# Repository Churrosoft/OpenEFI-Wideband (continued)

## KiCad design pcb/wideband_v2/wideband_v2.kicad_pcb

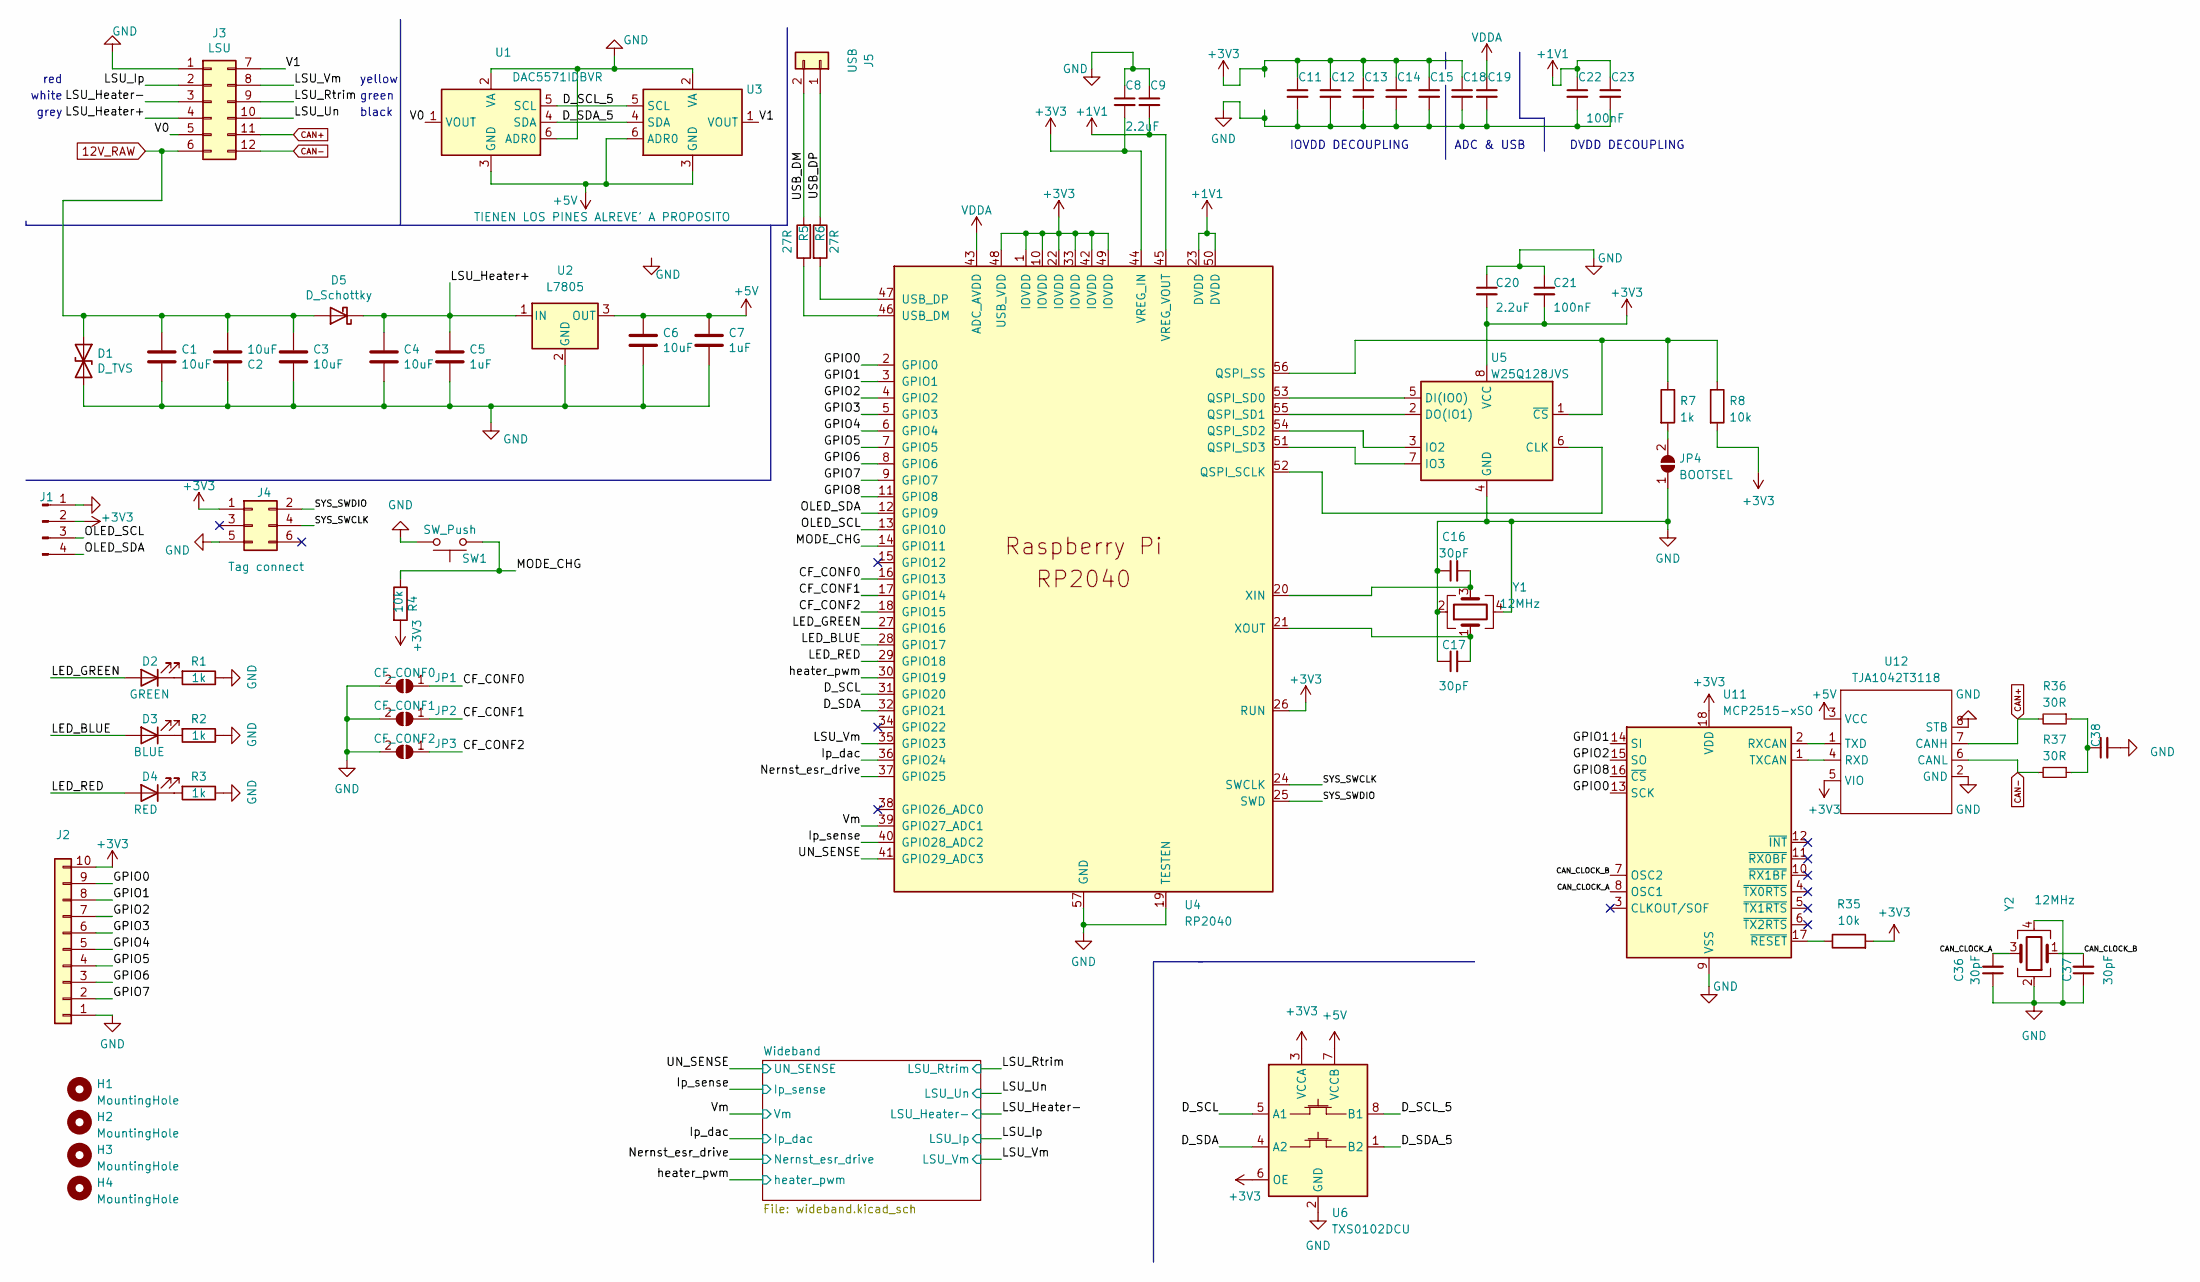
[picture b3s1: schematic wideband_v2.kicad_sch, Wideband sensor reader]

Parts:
C1, C2, C3, C4, C6: 10uF; C_1206_3216Metric; LCSC C13585
C5, C7: 1uF; C_0603_1608Metric; LCSC C15849
C8, C9, C20: 2.2uF; C_0603_1608Metric
C11, C12, C13, C14, C15, C18, C19, C21, C22, C23: 100nF; C_0603_1608Metric
C16, C17, C36, C37: 30pF; C_0603_1608Metric
C38: 4.7nF; C_0805_2012Metric; LCSC C77475
D1: D_TVS; D_SMC; LCSC C151279
D2: GREEN; LED_0603_1608Metric; LCSC C72043
D3: BLUE; LED_0603_1608Metric; LCSC C72041
D4: RED; LED_0603_1608Metric; LCSC C72041
D5: D_Schottky; D_SMA; LCSC C22452
H1, H2, H3, H4: MountingHole; MountingHole_2.2mm_M2
J1: DISPLAY; PinHeader_1x04_P2.54mm_Vertical
J2: GPIO; PinHeader_1x10_P2.00mm_Vertical
J3: LSU; Molex_Mini-Fit_Jr_5566-12A2_2x06_P4.20mm_Vertical
J4: Tag connect; Tag-Connect_TC2030-IDC-NL_2x03_P1.27mm_Vertical
J5: USB; PinHeader_1x02_P2.00mm_Vertical
JP1: CF_CONF0; SolderJumper-2_P1.3mm_Open_TrianglePad1.0x1.5mm
JP2: CF_CONF1; SolderJumper-2_P1.3mm_Open_TrianglePad1.0x1.5mm
JP3: CF_CONF2; SolderJumper-2_P1.3mm_Open_TrianglePad1.0x1.5mm
JP4: BOOTSEL; SolderJumper-2_P1.3mm_Open_TrianglePad1.0x1.5mm
R1, R2, R3, R7: 1k; R_0603_1608Metric
R4: 10k; R_0603_1608Metric; LCSC C25744
R5, R6: 27R; R_0603_1608Metric
R8, R35: 10k; R_0603_1608Metric
R36, R37: 30R; R_1206_3216Metric; LCSC C205298
SW1: SW_Push; SW_Tactile_SPST_Angled_PTS645Vx83-2LFS
U1: DAC5571IDBVR; SOT-23-6
U2: L7805; TO-220-3_Vertical
U3: DAC5571IDBVR; SOT-23-6; LCSC C24061
U4: RP2040; RP2040-QFN-56
U5: W25Q128JVS; SOIC-8_5.23x5.23mm_P1.27mm
U6: TXS0102DCU; VSSOP-8_2.3x2mm_P0.5mm
U11: MCP2515-xSO; SOIC-18W_7.5x11.6mm_P1.27mm
U12: TJA1042T3118; HTSOP-8-1EP_3.9x4.9mm_P1.27mm_EP2.4x3.2mm
Y1, Y2: 12MHz; Crystal_SMD_3225-4Pin_3.2x2.5mm; LCSC C9002

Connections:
12V_RAW: C1.1, C2.2, C3.1, D1.1 (A1), D5.2 (A), J3.6
+1V1: C9.2, C22.1, C23.1, U4.23 (DVDD), U4.45 (VREG_VOUT), U4.50 (DVDD)
+3V3: C8.2, C11.1, C12.1, C13.1, C14.1, C15.1, C18.1, C20.2, C21.2, J1.2, J2.10, J4.1, R4.2, R8.2, R35.2, U4.1 (IOVDD), U4.10 (IOVDD), U4.22 (IOVDD), U4.26 (RUN), U4.33 (IOVDD), U4.42 (IOVDD), U4.44 (VREG_IN), U4.48 (USB_VDD), U4.49 (IOVDD), U5.8 (VCC), U6.3 (VCCA), U6.6 (OE), U11.18 (VDD), U12.5 (VIO); also elsewhere on the board
+5V: C6.1, C7.1, U1.3 (GND), U2.3 (OUT), U3.3 (GND), U3.6 (ADR0), U6.7 (VCCB), U12.3 (VCC); also elsewhere on the board
/CAN_CLOCK_A: C36.2, U11.8 (OSC1), Y2.3
/CAN_CLOCK_B: C37.2, U11.7 (OSC2), Y2.1
/CF_CONF0: JP1.1 (A), U4.16 (GPIO13)
/CF_CONF1: JP2.1 (A), U4.17 (GPIO14)
/CF_CONF2: JP3.1 (A), U4.18 (GPIO15)
/D_SCL: U4.31 (GPIO20), U6.5 (A1)
/D_SCL_5: U1.5 (SCL), U3.5 (SCL), U6.8 (B1)
/D_SDA: U4.32 (GPIO21), U6.4 (A2)
/D_SDA_5: U1.4 (SDA), U3.4 (SDA), U6.1 (B2)
/GPIO0: J2.9, U4.2 (GPIO0), U11.13 (SCK)
/GPIO1: J2.8, U4.3 (GPIO1), U11.14 (SI)
/GPIO2: J2.7, U4.4 (GPIO2), U11.15 (SO)
/GPIO3: J2.6, U4.5 (GPIO3)
/GPIO4: J2.5, U4.6 (GPIO4)
/GPIO5: J2.4, U4.7 (GPIO5)
/GPIO6: J2.3, U4.8 (GPIO6)
/GPIO7: J2.2, U4.9 (GPIO7)
/GPIO8: U4.11 (GPIO8), U11.16 (~CS)
/Ip_dac: U4.36 (GPIO24); also elsewhere on the board
/Ip_sense: U4.40 (GPIO28_ADC2); also elsewhere on the board
/LED_BLUE: D3.2 (A), U4.28 (GPIO17)
/LED_GREEN: D2.2 (A), U4.27 (GPIO16)
/LED_RED: D4.2 (A), U4.29 (GPIO18)
/LSU_Heater+: C4.1, C5.1, D5.1 (K), J3.4, U2.1 (IN)
/LSU_Heater-: J3.3; also elsewhere on the board
/LSU_Ip: J3.2; also elsewhere on the board
/LSU_Rtrim: J3.9; also elsewhere on the board
/LSU_Un: J3.10; also elsewhere on the board
/LSU_Vm: J3.8, U4.35 (GPIO23); also elsewhere on the board
/MODE_CHG: R4.1, SW1.1, U4.14 (GPIO11)
/Nernst_esr_drive: U4.37 (GPIO25); also elsewhere on the board
/OLED_SCL: J1.3, U4.13 (GPIO10)
/OLED_SDA: J1.4, U4.12 (GPIO9)
/SYS_SWCLK: J4.4, U4.24 (SWCLK)
/SYS_SWDIO: J4.2, U4.25 (SWD)
/UN_SENSE: U4.41 (GPIO29_ADC3); also elsewhere on the board
/USB_DM: J5.2, R5.2
/USB_DP: J5.1, R6.1
/V0: J3.5, U1.1 (VOUT)
/V1: J3.7, U3.1 (VOUT)
/Vm: U4.39 (GPIO27_ADC1); also elsewhere on the board
/heater_pwm: U4.30 (GPIO19); also elsewhere on the board
CAN+: J3.11, R36.2, U12.7 (CANH)
CAN-: J3.12, R37.2, U12.6 (CANL)
GND: C1.2, C2.1, C3.2, C4.2, C5.2, C6.2, C7.2, C8.1, C9.1, C11.2, C12.2, C13.2, C14.2, C15.2, C16.1, C17.1, C18.2, C19.2, C20.1, C21.1, C22.2, C23.2, C36.1, C37.1, C38.2, D1.2 (A2), J1.1, J2.1, J3.1, J4.5, JP1.2 (B), JP2.2 (B), JP3.2 (B), JP4.1 (A), R1.1, R2.1, R3.1, SW1.2, U1.2 (VA), U1.6 (ADR0), U2.2 (GND), U3.2 (VA), U4.19 (TESTEN), U4.57 (GND), U5.4 (GND), U6.2 (GND), U11.9 (VSS), U12.2 (GND), U12.8 (STB), Y1.2, Y1.4, Y2.2, Y2.4; also elsewhere on the board
unnamed: C16.2, U4.20 (XIN), Y1.3
unnamed: C17.2, U4.21 (XOUT), Y1.1
unnamed: C38.1, R36.1, R37.1
unnamed: D2.1 (K), R1.2
unnamed: D3.1 (K), R2.2
unnamed: D4.1 (K), R3.2
unnamed: JP4.2 (B), R7.2
unnamed: R5.1, U4.46 (USB_DM)
unnamed: R6.2, U4.47 (USB_DP)
unnamed: R7.1, R8.1, U4.56 (QSPI_SS), U5.1 (~CS)
unnamed: R35.1, U11.17 (~RESET)
unnamed: U4.51 (QSPI_SD3), U5.7 (IO3)
unnamed: U4.52 (QSPI_SCLK), U5.6 (CLK)
unnamed: U4.53 (QSPI_SD0), U5.5 (DI(IO0))
unnamed: U4.54 (QSPI_SD2), U5.3 (IO2)
unnamed: U4.55 (QSPI_SD1), U5.2 (DO(IO1))
unnamed: U11.1 (TXCAN), U12.4 (RXD)
unnamed: U11.2 (RXCAN), U12.1 (TXD)
VDDA: C19.1, U4.43 (ADC_AVDD); also elsewhere on the board

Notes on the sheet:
grey
ADC & USB
black
white
red
IOVDD DECOUPLING
yellow
DVDD DECOUPLING
green

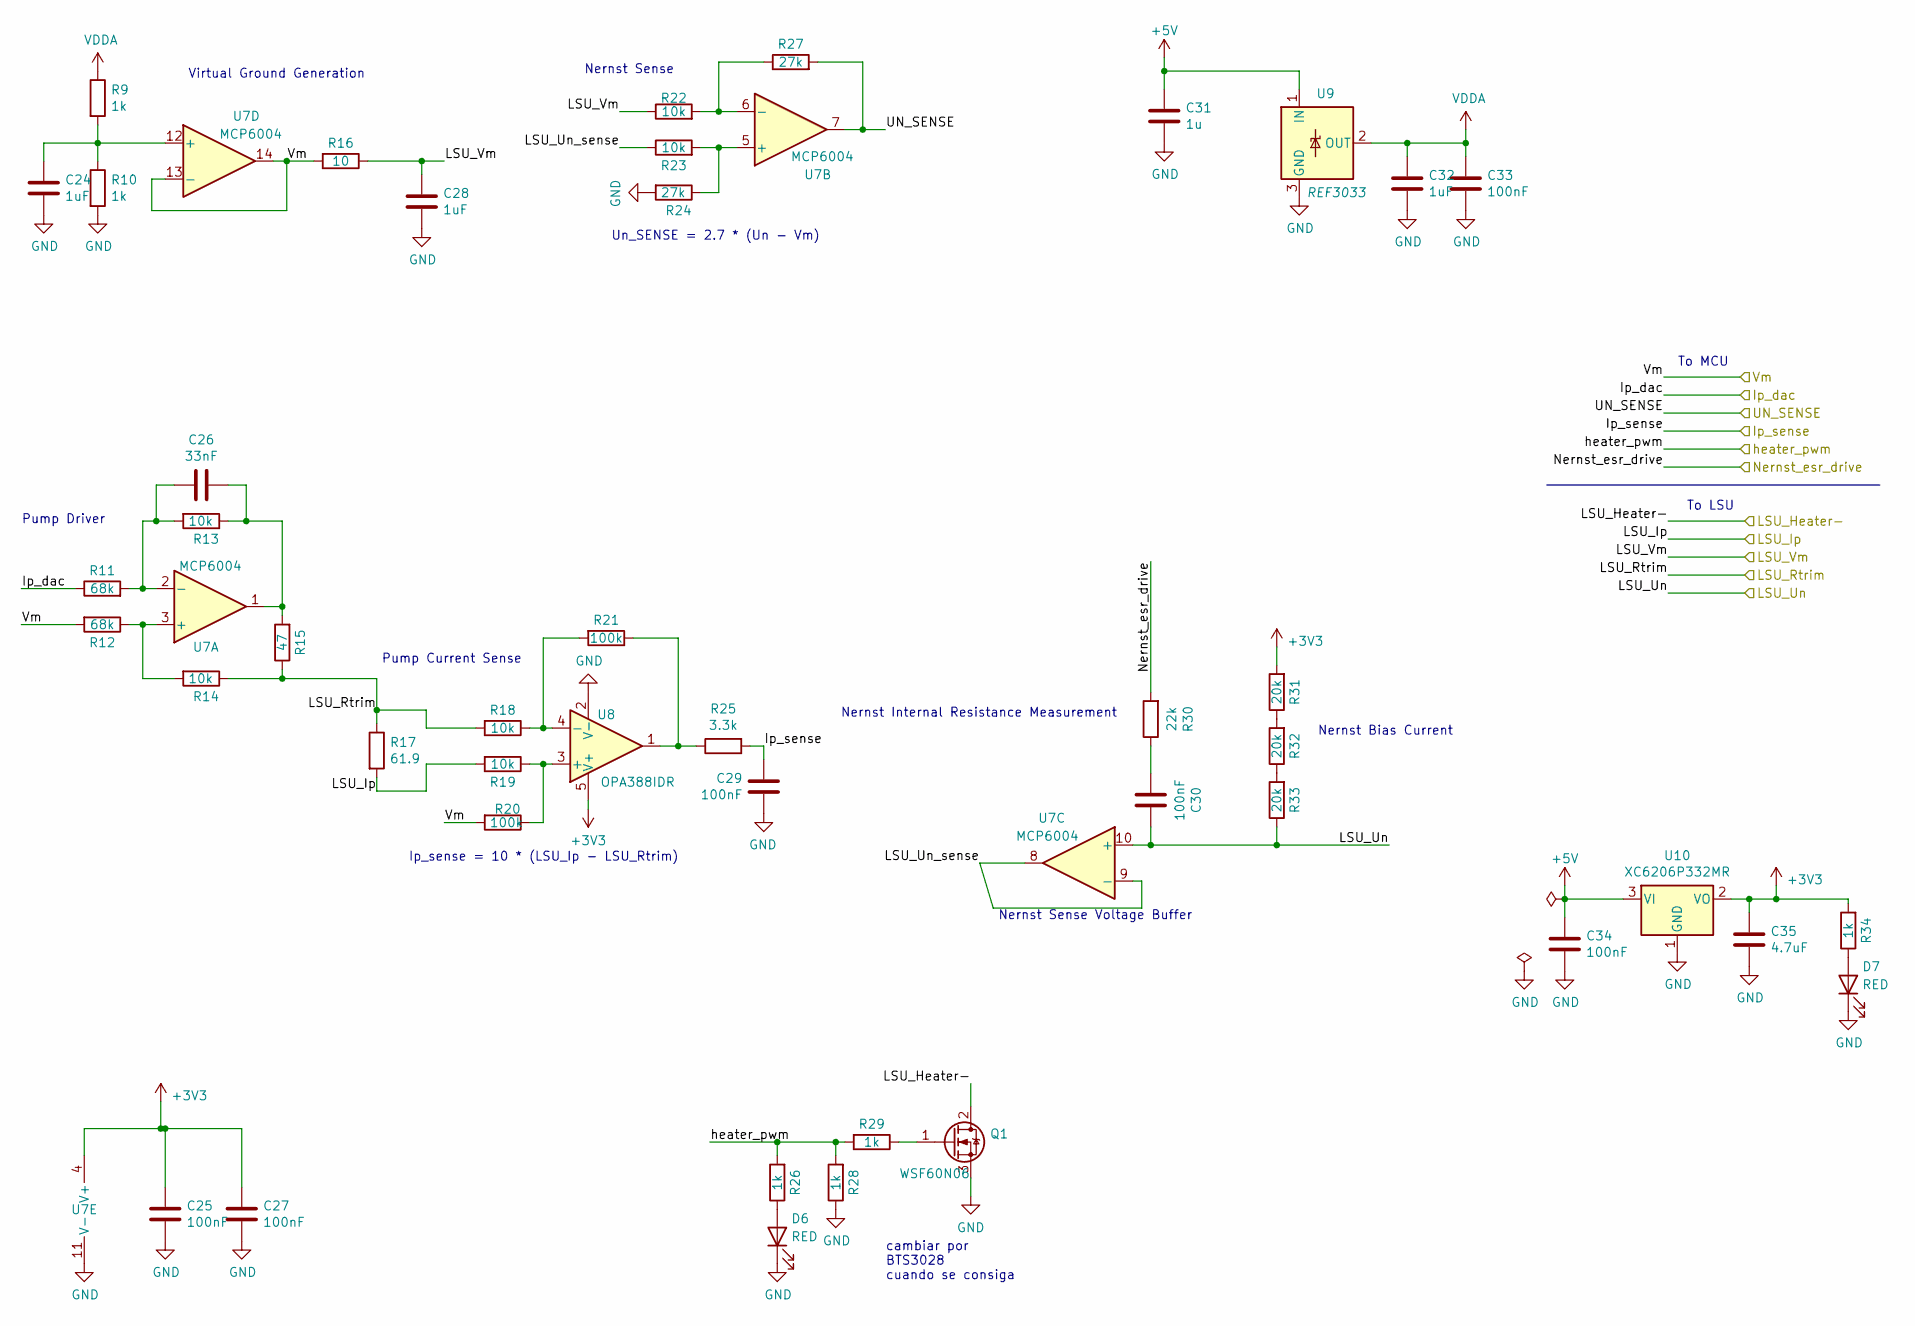
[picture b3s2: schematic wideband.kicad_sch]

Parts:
C24, C28, C32: 1uF; R_0603_1608Metric; LCSC C52923
C25, C27, C29, C30, C33, C34: 100nF; R_0603_1608Metric; LCSC C1525
C26: 33nF; R_0603_1608Metric; LCSC C1585
C31: 1u; R_0603_1608Metric; LCSC C52923
C35: 4.7uF; C_0603_1608Metric; LCSC C19666
D6, D7: RED; LED_0603_1608Metric; LCSC C2286
Q1: WSF60N06; TO-252-2; LCSC C148432
R9, R10, R26, R28, R29, R34: 1k; R_0603_1608Metric; LCSC C11702
R11, R12: 68k; R_0603_1608Metric; LCSC C36871
R13, R14, R18, R19, R22, R23: 10k; R_0603_1608Metric; LCSC C25744
R15: 47; R_0603_1608Metric; LCSC C25118
R16: 10; R_0603_1608Metric; LCSC C25077
R17: 61.9; R_0603_1608Metric; LCSC C23092
R20, R21: 100k; R_0603_1608Metric; LCSC C25741
R24, R27: 27k; R_0603_1608Metric; LCSC C25771
R25: 3.3k; R_0603_1608Metric; LCSC C25890
R30: 22k; R_0603_1608Metric; LCSC C25768
R31, R32, R33: 20k; R_0603_1608Metric; LCSC C25765
U7: MCP6004; TSSOP-14_4.4x5mm_P0.65mm; LCSC C50282
U8: OPA388IDR; TSOT-23-5; LCSC C154118
U9: REF3033; SOT-23; LCSC C36658
U10: XC6206P332MR; SOT-23; LCSC C5446

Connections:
+3V3: C25.1, C27.1, C35.1, R31.2, R34.2, U7.4 (V+), U8.5 (V+), U10.2 (VO); also elsewhere on the board
+5V: C31.1, C34.1, U9.1 (IN), U10.3 (VI); also elsewhere on the board
/Ip_dac: R11.1; also elsewhere on the board
/Ip_sense: C29.1, R25.2; also elsewhere on the board
/LSU_Heater-: Q1.2 (D); also elsewhere on the board
/LSU_Ip: R17.2, R19.2; also elsewhere on the board
/LSU_Rtrim: R14.1, R15.1, R17.1, R18.2; also elsewhere on the board
/LSU_Un: C30.1, R33.1, U7.10 (+); also elsewhere on the board
/LSU_Vm: C28.1, R16.1, R22.1; also elsewhere on the board
/Nernst_esr_drive: R30.2; also elsewhere on the board
/UN_SENSE: R27.2, U7.7; also elsewhere on the board
/Vm: R12.2, R16.2, R20.2, U7.13 (-), U7.14; also elsewhere on the board
/Wideband/LSU_Un_sense: R23.1, U7.8, U7.9 (-)
/heater_pwm: R26.2, R28.2, R29.2; also elsewhere on the board
GND: C24.2, C25.2, C27.2, C28.2, C29.2, C31.2, C32.2, C33.2, C34.2, C35.2, D6.1 (K), D7.1 (K), Q1.3 (S), R10.2, R24.2, R28.1, U7.11 (V-), U8.2 (V-), U9.3 (GND), U10.1 (GND); also elsewhere on the board
unnamed: C24.1, R9.2, R10.1, U7.12 (+)
unnamed: C26.1, R13.1, R15.2, U7.1
unnamed: C26.2, R11.2, R13.2, U7.2 (-)
unnamed: C30.2, R30.1
unnamed: D6.2 (A), R26.1
unnamed: D7.2 (A), R34.1
unnamed: Q1.1 (G), R29.1
unnamed: R12.1, R14.2, U7.3 (+)
unnamed: R18.1, R21.2, U8.4 (-)
unnamed: R19.1, R20.1, U8.3 (+)
unnamed: R21.1, R25.1, U8.1
unnamed: R22.2, R27.1, U7.6 (-)
unnamed: R23.2, R24.1, U7.5 (+)
unnamed: R31.1, R32.2
unnamed: R32.1, R33.2
VDDA: C32.1, C33.1, R9.1, U9.2 (OUT); also elsewhere on the board

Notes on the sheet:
Nernst Sense
Nernst Internal Resistance Measurement
Virtual Ground Generation
To LSU
Nernst Sense Voltage Buffer
Nernst Bias Current
Pump Driver
cambiar por BTS3028 cuando se consiga
Ip_sense = 10 * (LSU_Ip - LSU_Rtrim)
To MCU
Un_SENSE = 2.7 * (Un - Vm)
Pump Current Sense

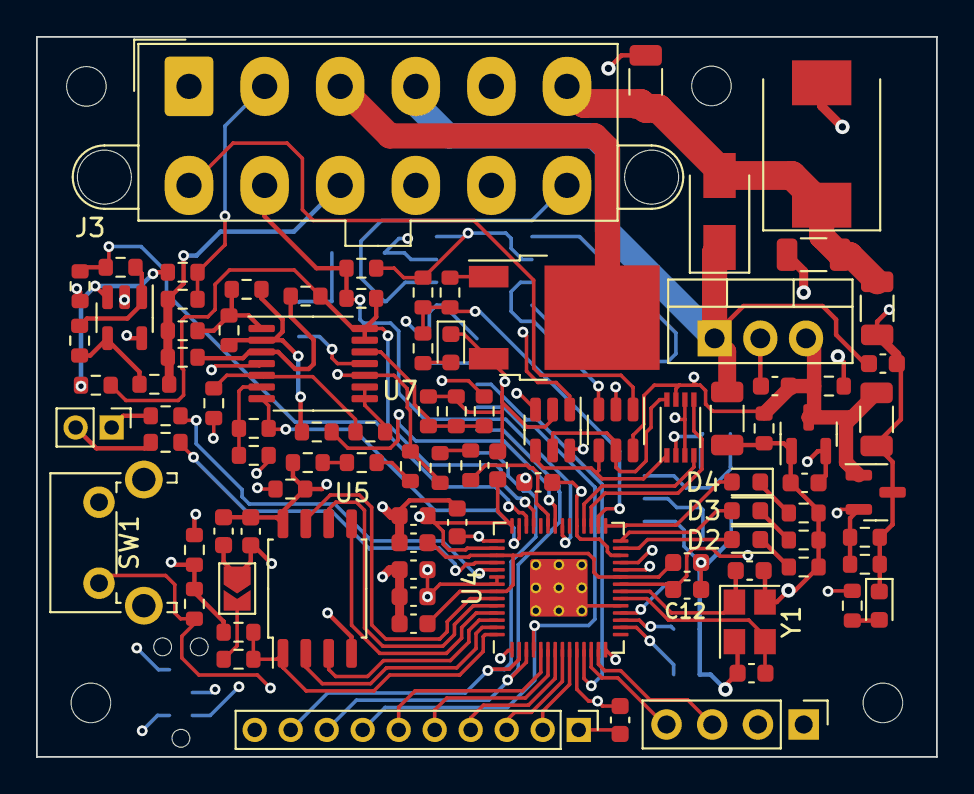
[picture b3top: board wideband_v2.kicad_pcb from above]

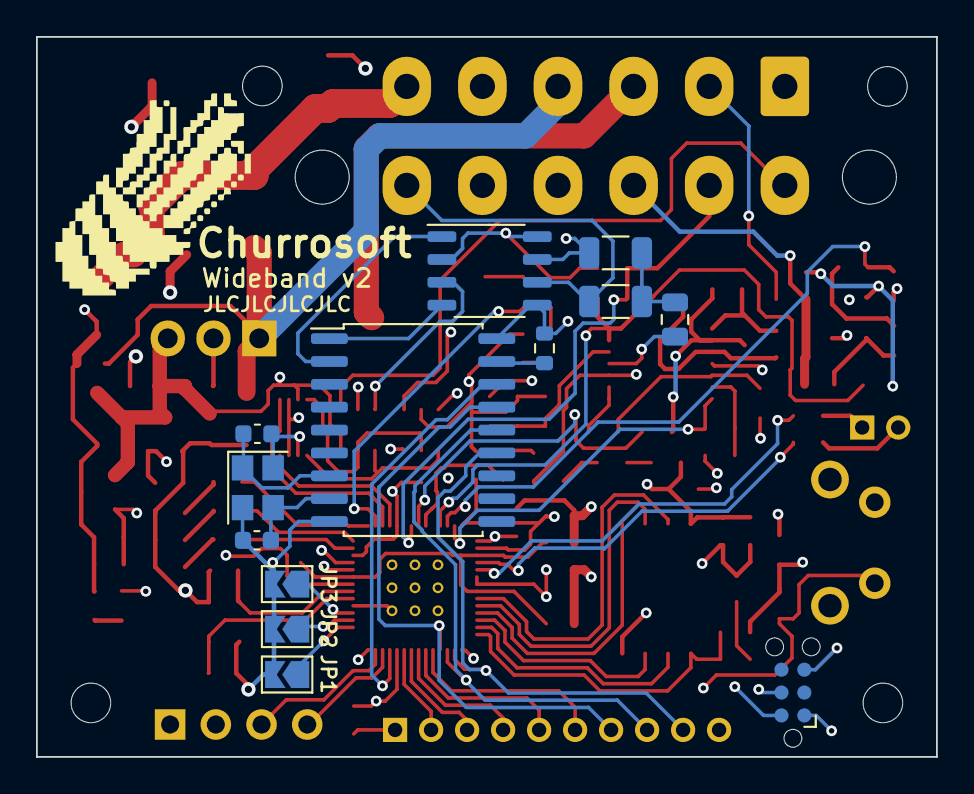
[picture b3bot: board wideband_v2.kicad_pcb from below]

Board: 4 copper layers, 50.0 x 40.0 mm, 111 parts (14 on the bottom side), 84 nets.

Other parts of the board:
Churrosoft: SYM_Hot_Large; churro_new_v4

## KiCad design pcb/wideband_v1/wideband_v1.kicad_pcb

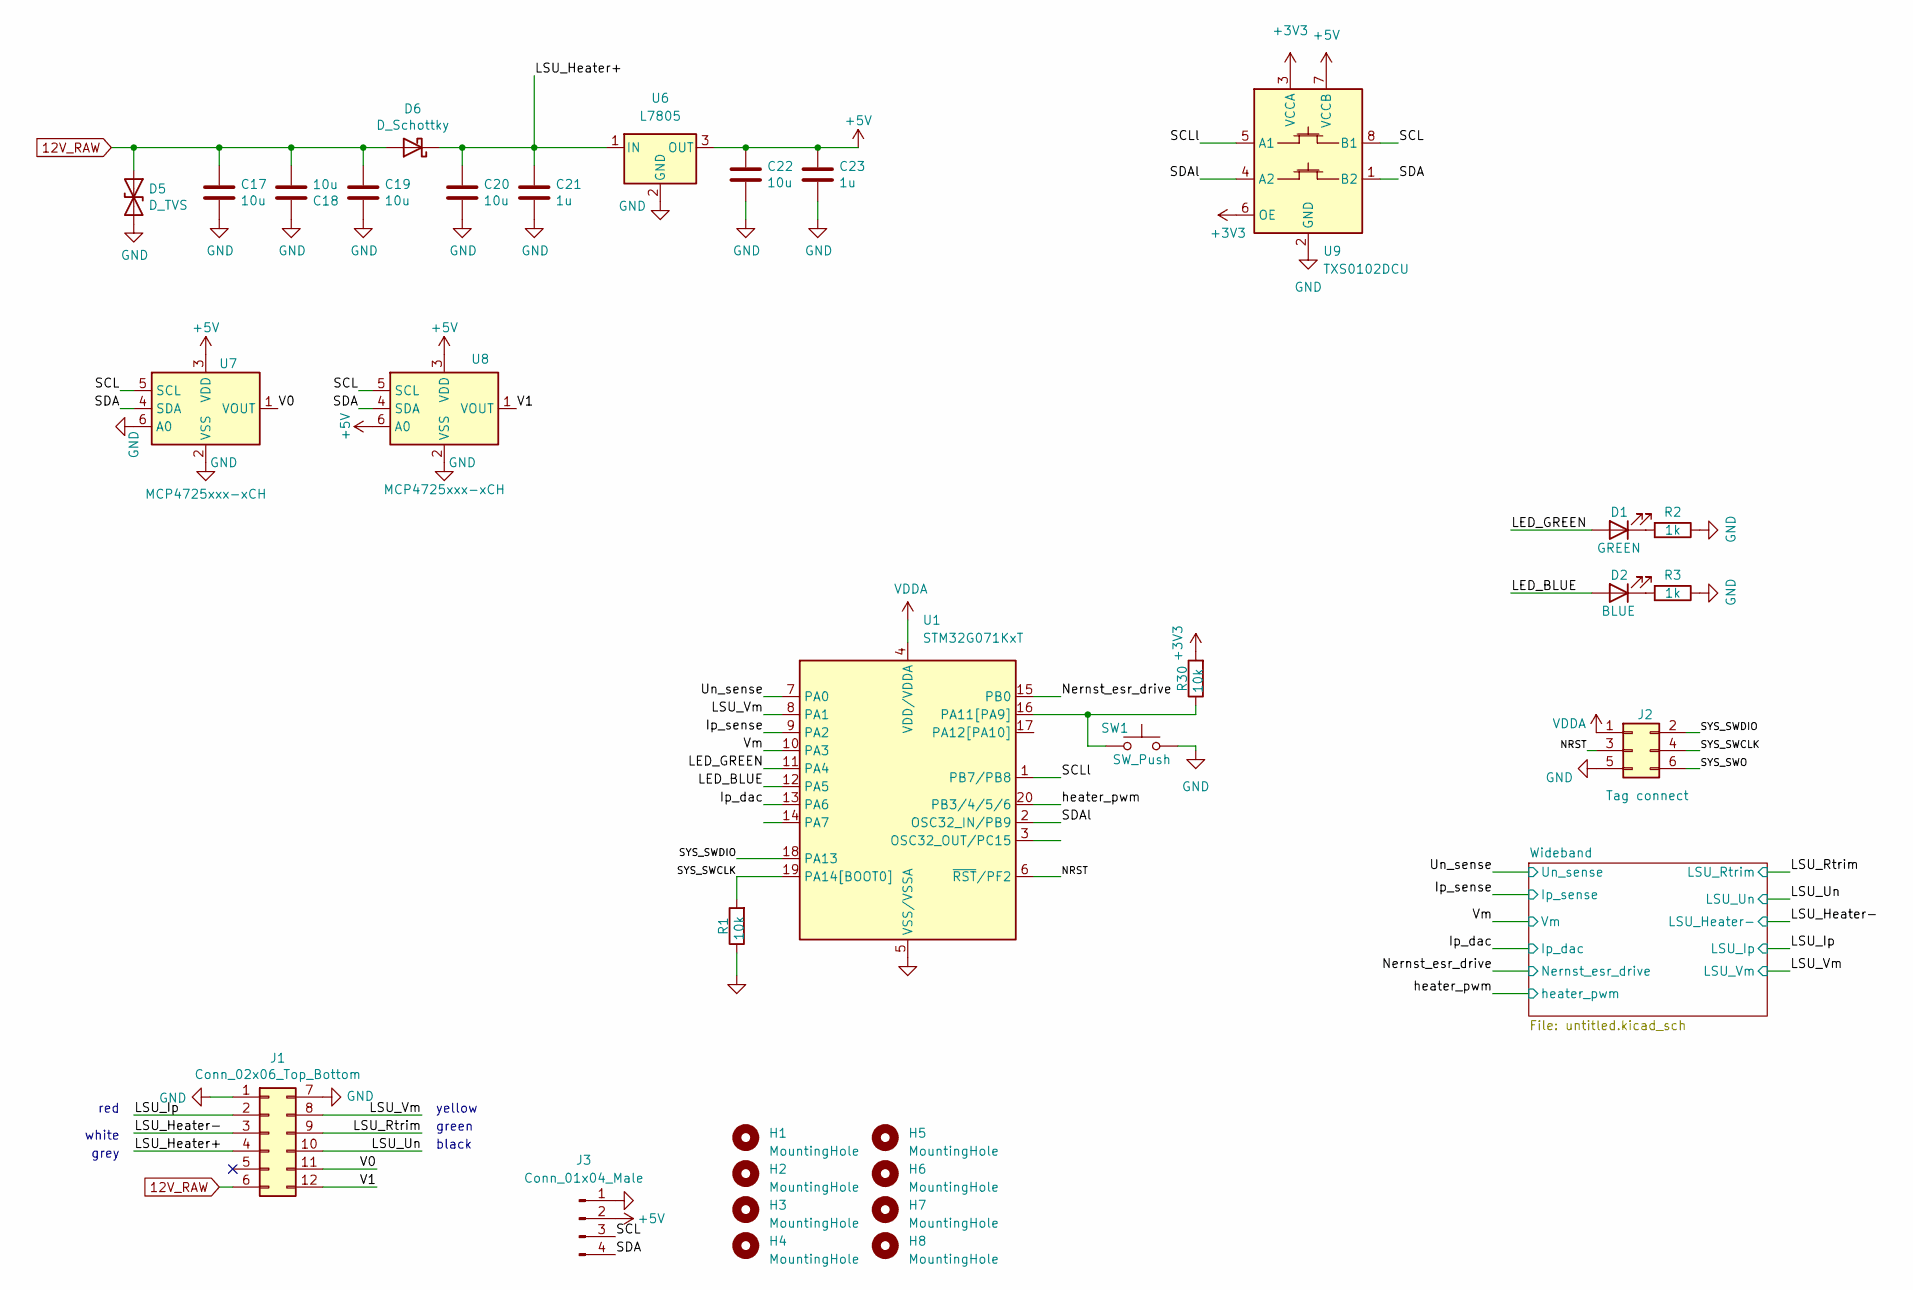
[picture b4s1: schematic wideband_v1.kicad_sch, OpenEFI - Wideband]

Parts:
C17, C18, C19, C20, C22: 10u; C_1206_3216Metric; LCSC C13585
C21, C23: 1u; C_0603_1608Metric; LCSC C15849
D1: GREEN; LED_0603_1608Metric; LCSC C72043
D2: BLUE; LED_0603_1608Metric; LCSC C72041
D5: D_TVS; D_SMC; LCSC C151279
D6: D_Schottky; D_SMA; LCSC C22452
H1, H2, H3, H4: MountingHole; MountingHole_2.2mm_M2
H5, H6, H7, H8: MountingHole; Fiducial_1mm_Mask2mm
J1: Conn_02x06_Top_Bottom; Molex_Mini-Fit_Jr_5566-12A2_2x06_P4.20mm_Vertical
J2: Tag connect; Tag-Connect_TC2030-IDC-NL_2x03_P1.27mm_Vertical
J3: Conn_01x04_Male; PinHeader_1x04_P2.54mm_Vertical
R1, R30: 10k; R_0603_1608Metric; LCSC C25744
R2, R3: 1k; R_0603_1608Metric; LCSC C11702
SW1: SW_Push; SW_Tactile_SPST_Angled_PTS645Vx83-2LFS
U1: STM32G071KxT; TSSOP-20_4.4x6.5mm_P0.65mm
U6: L7805; TO-220-3_Vertical
U7, U8: MCP4725xxx-xCH; SOT-23-6
U9: TXS0102DCU; VSSOP-8_2.3x2mm_P0.5mm

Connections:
12V_RAW: C17.1, C18.2, C19.1, D5.1 (A1), D6.2 (A), J1.6
+5V: C22.1, C23.1, J3.2, U6.3 (OUT), U7.3 (VDD), U8.3 (VDD), U8.6 (A0), U9.7 (VCCB); also elsewhere on the board
/Ip_dac: U1.13 (PA6); also elsewhere on the board
/Ip_sense: U1.9 (PA2); also elsewhere on the board
/LED_BLUE: D2.2 (A), U1.12 (PA5)
/LED_GREEN: D1.2 (A), U1.11 (PA4)
/LSU_Heater+: C20.1, C21.1, D6.1 (K), J1.4, U6.1 (IN)
/LSU_Heater-: J1.3; also elsewhere on the board
/LSU_Ip: J1.2; also elsewhere on the board
/LSU_Rtrim: J1.9; also elsewhere on the board
/LSU_Un: J1.10; also elsewhere on the board
/LSU_Vm: J1.8, U1.8 (PA1); also elsewhere on the board
/NRST: J2.3, U1.6 (~RST/PF2)
/Nernst_esr_drive: U1.15 (PB0); also elsewhere on the board
/SCL: J3.3, U7.5 (SCL), U8.5 (SCL), U9.8 (B1)
/SCLl: U1.1 (PB7/PB8), U9.5 (A1)
/SDA: J3.4, U7.4 (SDA), U8.4 (SDA), U9.1 (B2)
/SDAl: U1.2 (OSC32_IN/PB9), U9.4 (A2)
/SYS_SWCLK: J2.4, R1.2, U1.19 (PA14[BOOT0])
/SYS_SWDIO: J2.2, U1.18 (PA13)
/SYS_SWO: J2.6
/Un_sense: U1.7 (PA0); also elsewhere on the board
/V0: J1.11, U7.1 (VOUT)
/V1: J1.12, U8.1 (VOUT)
/Vm: U1.10 (PA3); also elsewhere on the board
/heater_pwm: U1.20 (PB3/4/5/6); also elsewhere on the board
GND: C17.2, C18.1, C19.2, C20.2, C21.2, C22.2, C23.2, D5.2 (A2), J1.1, J1.7, J2.5, J3.1, R1.1, R2.1, R3.1, SW1.2, U1.5 (VSS/VSSA), U6.2 (GND), U7.2 (VSS), U7.6 (A0), U8.2 (VSS), U9.2 (GND); also elsewhere on the board
unnamed: D1.1 (K), R2.2
unnamed: D2.1 (K), R3.2
unnamed: R30.1, SW1.1, U1.16 (PA11[PA9])
VDDA: J2.1, U1.4 (VDD/VDDA); also elsewhere on the board

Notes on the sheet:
white
yellow
black
green
red
grey

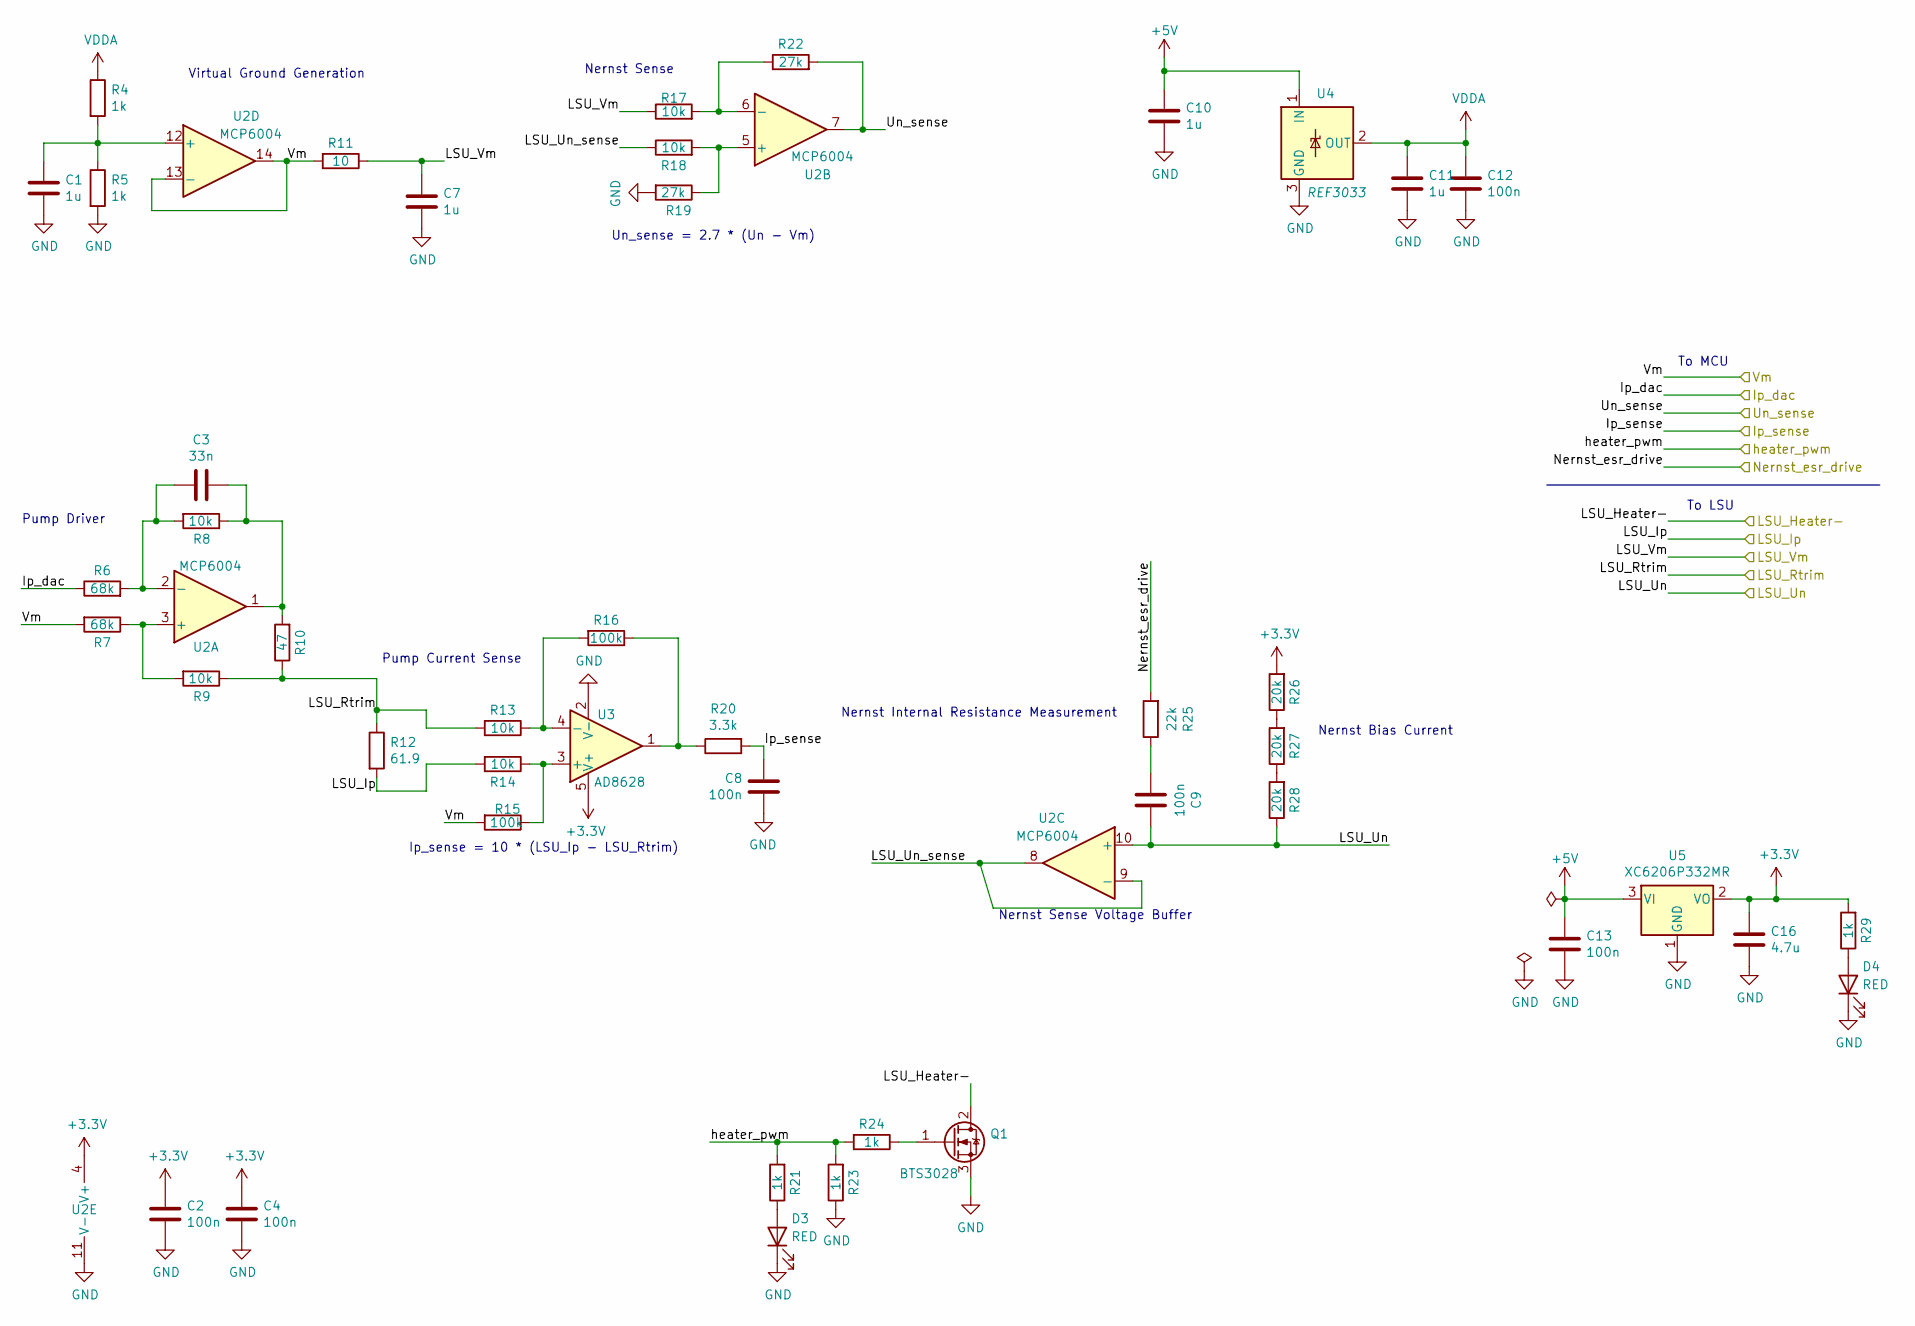
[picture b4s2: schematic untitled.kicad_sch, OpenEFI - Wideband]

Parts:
C1, C7, C10, C11: 1u; R_0603_1608Metric; LCSC C52923
C2, C4, C8, C9, C12, C13: 100n; R_0603_1608Metric; LCSC C1525
C3: 33n; R_0603_1608Metric; LCSC C1585
C16: 4.7u; C_0603_1608Metric; LCSC C19666
D3, D4: RED; LED_0603_1608Metric; LCSC C2286
Q1: BTS3028; TO-252-2; LCSC C112639
R4, R5, R21, R23, R24, R29: 1k; R_0603_1608Metric; LCSC C11702
R6, R7: 68k; R_0603_1608Metric; LCSC C36871
R8, R9, R13, R14, R17, R18: 10k; R_0603_1608Metric; LCSC C25744
R10: 47; R_0603_1608Metric; LCSC C25118
R11: 10; R_0603_1608Metric; LCSC C25077
R12: 61.9; R_0603_1608Metric; LCSC C23092
R15, R16: 100k; R_0603_1608Metric; LCSC C25741
R19, R22: 27k; R_0603_1608Metric; LCSC C25771
R20: 3.3k; R_0603_1608Metric; LCSC C25890
R25: 22k; R_0603_1608Metric; LCSC C25768
R26, R27, R28: 20k; R_0603_1608Metric; LCSC C25765
U2: MCP6004; TSSOP-14_4.4x5mm_P0.65mm; LCSC C50282
U3: AD8628; TSOT-23-5; LCSC C29309
U4: REF3033; SOT-23; LCSC C36658
U5: XC6206P332MR; SOT-23; LCSC C5446

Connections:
+5V: C10.1, C13.1, U4.1 (IN), U5.3 (VI); also elsewhere on the board
/Ip_dac: R6.1; also elsewhere on the board
/Ip_sense: C8.1, R20.2; also elsewhere on the board
/LSU_Heater-: Q1.2 (D); also elsewhere on the board
/LSU_Ip: R12.2, R14.2; also elsewhere on the board
/LSU_Rtrim: R9.1, R10.1, R12.1, R13.2; also elsewhere on the board
/LSU_Un: C9.1, R28.1, U2.10 (+); also elsewhere on the board
/LSU_Vm: C7.1, R11.1, R17.1; also elsewhere on the board
/Nernst_esr_drive: R25.2; also elsewhere on the board
/Un_sense: R22.2, U2.7; also elsewhere on the board
/Vm: R7.2, R11.2, R15.2, U2.13 (-), U2.14; also elsewhere on the board
/Wideband/LSU_Un_sense: R18.1, U2.8, U2.9 (-)
/heater_pwm: R21.2, R23.2, R24.2; also elsewhere on the board
GND: C1.2, C2.2, C4.2, C7.2, C8.2, C10.2, C11.2, C12.2, C13.2, C16.2, D3.1 (K), D4.1 (K), Q1.3 (S), R5.2, R19.2, R23.1, U2.11 (V-), U3.2 (V-), U4.3 (GND), U5.1 (GND); also elsewhere on the board
unnamed: C1.1, R4.2, R5.1, U2.12 (+)
unnamed: C3.1, R8.1, R10.2, U2.1
unnamed: C3.2, R6.2, R8.2, U2.2 (-)
unnamed: C9.2, R25.1
unnamed: D3.2 (A), R21.1
unnamed: D4.2 (A), R29.1
unnamed: Q1.1 (G), R24.1
unnamed: R7.1, R9.2, U2.3 (+)
unnamed: R13.1, R16.2, U3.4 (-)
unnamed: R14.1, R15.1, U3.3 (+)
unnamed: R16.1, R20.1, U3.1
unnamed: R17.2, R22.1, U2.6 (-)
unnamed: R18.2, R19.1, U2.5 (+)
unnamed: R26.1, R27.2
unnamed: R27.1, R28.2
VDDA: C11.1, C12.1, R4.1, U4.2 (OUT); also elsewhere on the board

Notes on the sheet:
Virtual Ground Generation
Ip_sense = 10 * (LSU_Ip - LSU_Rtrim)
To MCU
Un_sense = 2.7 * (Un - Vm)
To LSU
Pump Driver
Nernst Bias Current
Nernst Internal Resistance Measurement
Nernst Sense
Nernst Sense Voltage Buffer
Pump Current Sense

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
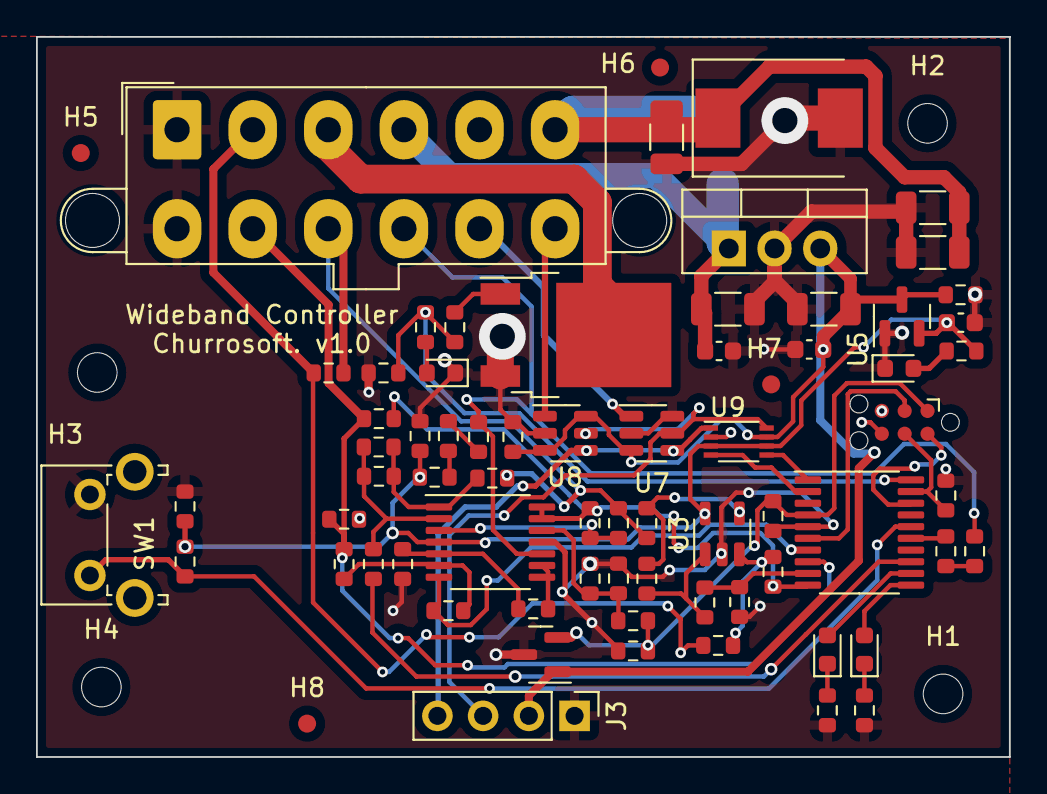
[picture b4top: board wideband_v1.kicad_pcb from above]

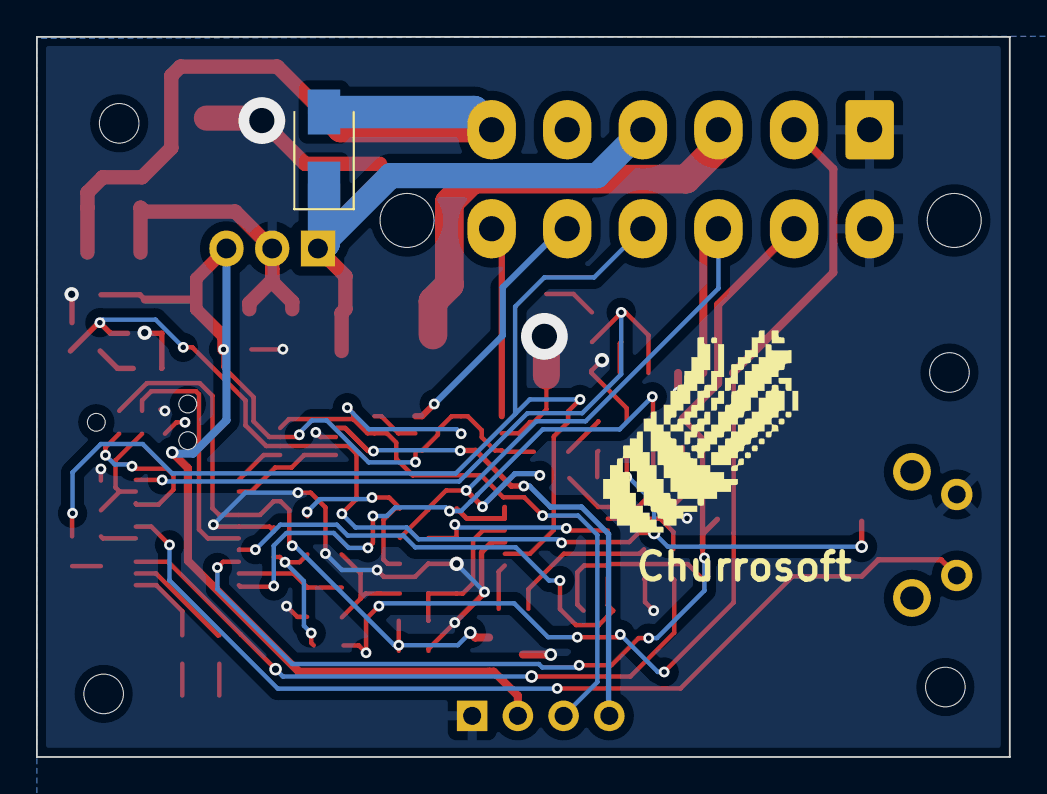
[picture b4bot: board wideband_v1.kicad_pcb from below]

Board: 2 copper layers, 54.1 x 40.0 mm, 79 parts (2 on the bottom side), 47 nets.

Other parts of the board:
Churrosoft: SYM_Hot_Large; churro_new_v4
Churrosoft#2: SYM_Hot_Large; churro_new_v4

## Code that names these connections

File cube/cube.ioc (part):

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Mcu.Name=STM32G030F6Px
Mcu.Package=TSSOP20
Mcu.UserName=STM32G030F6Px
PA0.GPIOParameters=GPIO_Label
PA0.GPIO_Label=Un_sense
PA0.Mode=IN0
PA0.Signal=ADC1_IN0
PA1.GPIOParameters=GPIO_Label
PA1.GPIO_Label=LSU_Vm
PA1.Mode=IN1
PA1.Signal=ADC1_IN1
PA13.Mode=Serial_Wire
PA13.Signal=SYS_SWDIO
PA14-BOOT0.Mode=Serial_Wire
PA14-BOOT0.Signal=SYS_SWCLK
PA2.GPIOParameters=GPIO_Label
PA2.GPIO_Label=LSU_Vm
PA2.Mode=IN2
PA2.Signal=ADC1_IN2
PA3.GPIOParameters=GPIO_Label
PA3.GPIO_Label=Vm
PA3.Mode=IN3
PA3.Signal=ADC1_IN3
PA4.GPIOParameters=GPIO_Label
PA4.GPIO_Label=LED_RED
PA4.Signal=GPIO_Output
PA5.GPIOParameters=GPIO_Label
PA5.GPIO_Label=LED_GREEN
PA5.Signal=GPIO_Output
PA6.GPIOParameters=GPIO_Label
PA6.GPIO_Label=Ip_dac
PA6.Signal=S_TIM3_CH1
PA7.GPIOParameters=GPIO_Label
PA7.GPIO_Label=LED_ZEPPELIN
PA7.Signal=GPIO_Output
PB0.GPIOParameters=GPIO_Label
PB0.GPIO_Label=Nernst_esr_drive
PB0.Signal=GPIO_Output
PB3.GPIOParameters=GPIO_Label
PB3.GPIO_Label=heater_pwm
PB3.Signal=S_TIM1_CH2
PB8.Mode=I2C
PB8.Signal=I2C1_SCL
PB9.Mode=I2C
PB9.Signal=I2C1_SDA
RCC.HSE_VALUE=8000000
RCC.SYSCLKFreq_VALUE=64000000
RCC.SYSCLKSource=RCC_SYSCLKSOURCE_PLLCLK
board=custom

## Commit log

2022-03-07 v1 of pcb
2022-07-08 init rp2040 firmware, added heater_control basis
2022-07-10 added heater control state machine
2022-07-12 Wideband v2
2022-07-12 Updating BOM SKUs
2022-07-12 MCP4725 => DAC5571
2022-07-12 Fix SKUs. Upload JLC database
2022-07-12 BTS3028 => WSF60N06 | AD8628 => OPA388IDR
2022-07-12 added heater thread
2022-07-12 tune tracks/vias
2022-07-13 add CAN controller
2022-07-13 trace external i/o
2022-07-13 Routing
2023-11-29 created v3 sch
2023-11-30 update pcb layout
2023-12-04 init 7seg pcb
2023-12-05 Cosas
2023-12-05 Code SKUs
2023-12-05 rev3, reduce extended component count
2023-12-05 Optimize SKUs
2023-12-05 Update gitignore
2023-12-05 update DAC for v3
2023-12-05 update 7seg footprint
2023-12-06 rev3: update connector on main board
2023-12-06 Bug fixes and enhancements
2023-12-06 update transistors on rev3
2024-03-22 update LCSC/Stock codes, update pcb to new footprints
2024-04-07 init fw
2024-04-08 init can code
2024-04-10 init canbus code for wbo module
2024-04-12 reorganize rev3 diagram, add display code to carrier fw
2024-04-17 ya ni me acuerdo que hice, pero seguro era algo del display
2024-04-23 fix can not starting
2024-08-19 wip carrier fw
2024-08-20 valid lambda print
